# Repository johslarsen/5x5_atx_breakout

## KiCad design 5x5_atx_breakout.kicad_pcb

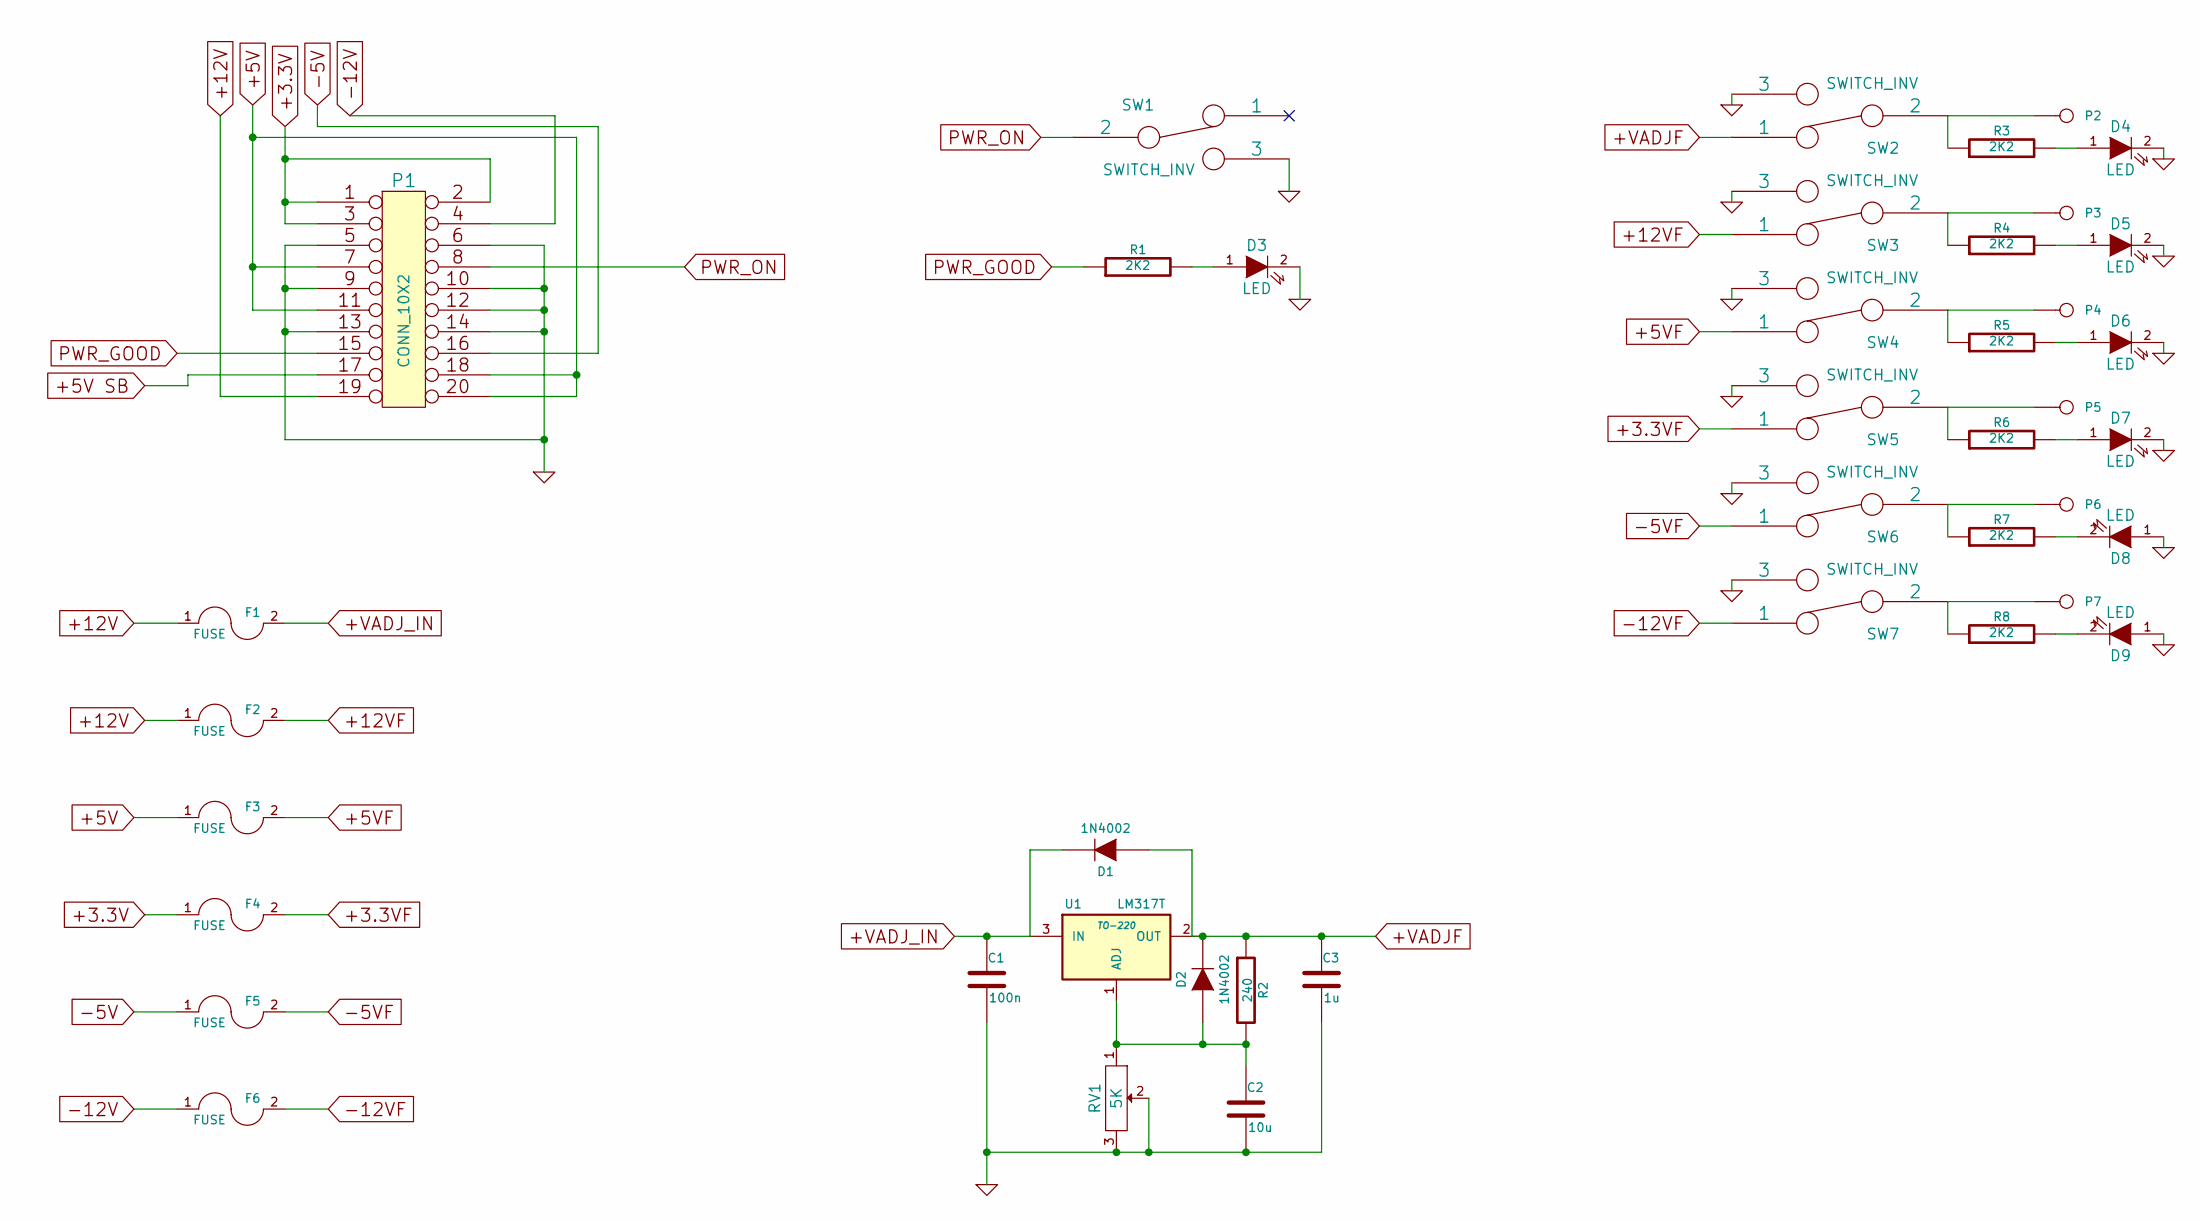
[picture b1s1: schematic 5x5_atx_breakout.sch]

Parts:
C1: 100n
C2: 10u
C3: 1u
D1, D2: 1N4002
D3, D4, D5, D6, D7, D8, D9: LED
F1, F2, F3, F4, F5, F6: FUSE
P1: CONN_10X2
P2, P3, P4, P5, P6, P7: CONN_1
R1, R3, R4, R5, R6, R7, R8: 2K2
R2: 240
RV1: 5K
SW1, SW2, SW3, SW4, SW5, SW6, SW7: SWITCH_INV
U1: LM317T; TO-220

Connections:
+3.3V: F4.1, P1.1, P1.2, P1.3
+3.3VF: F4.2, SW5.1
+5V: F3.1, P1.7, P1.11, P1.18, P1.20
+5VF: F3.2, SW4.1
+12V: F1.1, F2.1, P1.19
+12VF: F2.2, SW3.1
+VADJF: C3.1, D1.1 (A), D2.2 (K), R2.1, SW2.1, U1.2 (OUT)
+VADJ_IN: C1.1, D1.2 (K), F1.2, U1.3 (IN)
-5V: F5.1, P1.16
-5VF: F5.2, SW6.1
-12V: F6.1, P1.4
-12VF: F6.2, SW7.1
GND: C1.2, C2.2, C3.2, D3.2 (K), D4.2 (K), D5.2 (K), D6.2 (K), D7.2 (K), D8.1 (A), D9.1 (A), P1.5, P1.6, P1.9, P1.10, P1.12, P1.13, P1.14, RV1.2, RV1.3, SW1.3, SW2.3, SW3.3, SW4.3, SW5.3, SW6.3, SW7.3
unnamed: D8.2 (K), R7.2
unnamed: P6.1, R7.1, SW6.2
unnamed: D7.1 (A), R6.2
unnamed: P5.1, R6.1, SW5.2
unnamed: D6.1 (A), R5.2
unnamed: P4.1, R5.1, SW4.2
unnamed: D5.1 (A), R4.2
unnamed: P3.1, R4.1, SW3.2
unnamed: D4.1 (A), R3.2
unnamed: P2.1, R3.1, SW2.2
unnamed: D9.2 (K), R8.2
unnamed: P7.1, R8.1, SW7.2
unnamed: D3.1 (A), R1.2
unnamed: C2.1, D2.1 (A), R2.2, RV1.1, U1.1 (ADJ)
PWR_GOOD: P1.15, R1.1
PWR_ON: P1.8, SW1.2

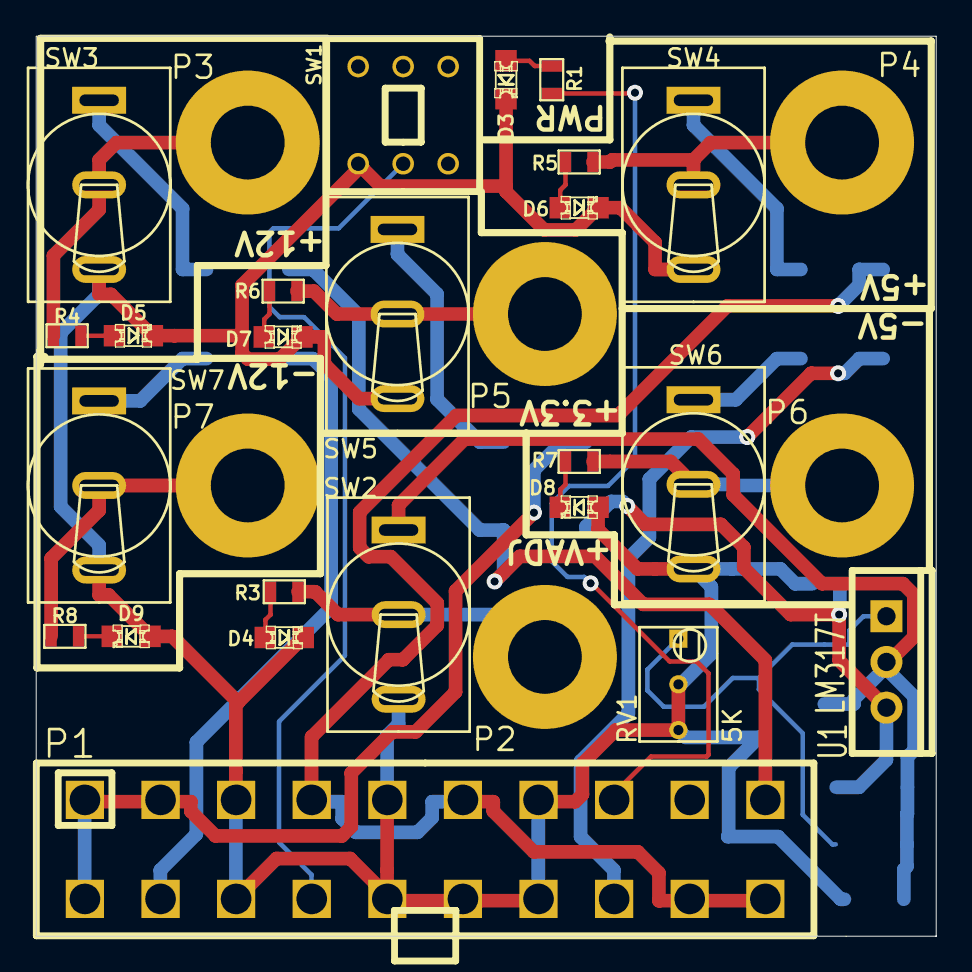
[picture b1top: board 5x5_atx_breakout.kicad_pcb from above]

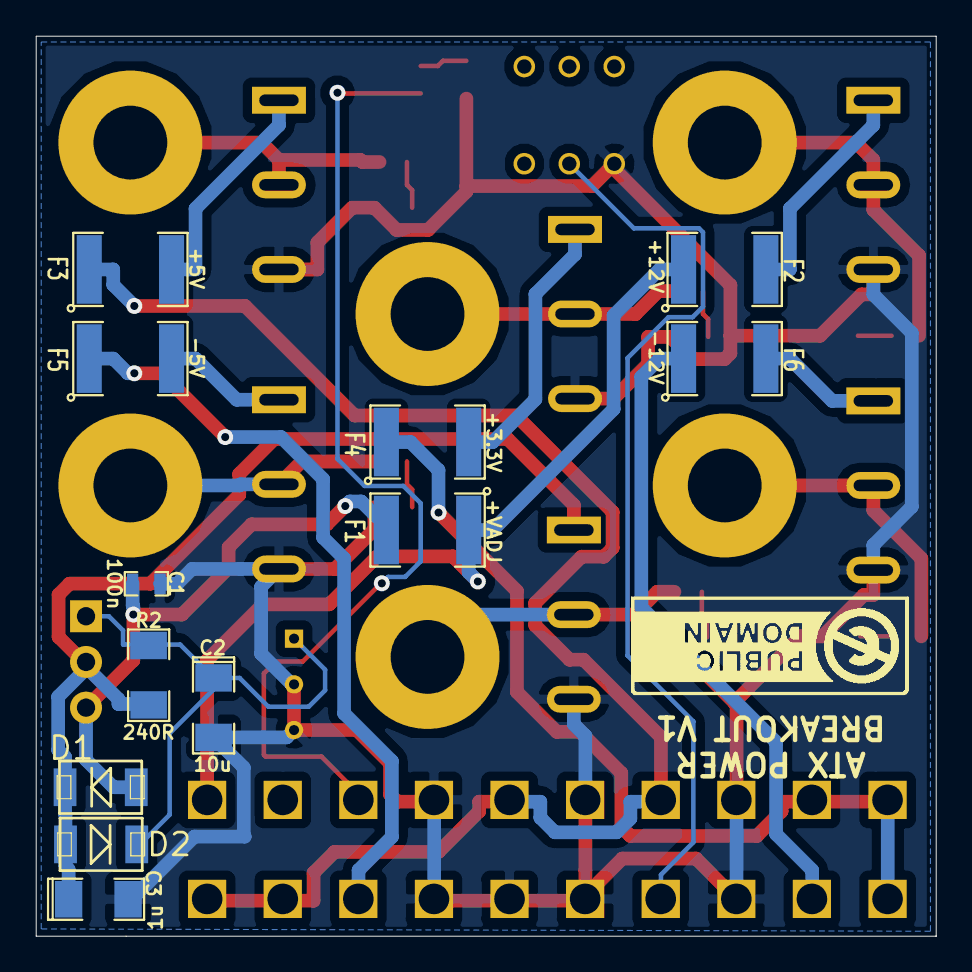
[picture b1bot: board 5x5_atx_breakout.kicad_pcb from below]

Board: 2 copper layers, 50.0 x 50.0 mm, 42 parts (12 on the bottom side), 29 nets.

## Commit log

2014-08-04 added submodule lib_kicad
2014-09-07 completed v1
2014-09-08 standardized the pcb text thickness to 0.25mm for title, usage info,... and 0.125mm (dirtypcbs.com minimum) for other stuff and moved text so that references is not hidden by components
2014-09-11 added public domain license
2014-09-11 added v1 gerbers sent to dirtypcbs.com
